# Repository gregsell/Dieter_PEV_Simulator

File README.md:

# dieter for EVerest PEV simulator
The EVerest PEV Simulator project documentation is split in two repositories:
1. the EVerest software running on linux, available at [gregsell/DieterEvDriver](https://github.com/gregsell/DieterEvDriver/)
2. this repo: electronics and firmware of the "Dieter" handling low level communication - *" Device Interface ElecTronic Especially not limited to Raspberry"*

demo: https://youtu.be/5YWvrdBq7K8?si=sz70jL9PTbtog_6K  
An essay covering the whole project is available under [gregsell/DieterEvDriver/docs/](https://github.com/gregsell/DieterEvDriver/) in english and german.  

## Hardware and Firmware for the Dieter PEV Simulator Board

This board is a physical interface between the [EVerest PEV Simulator](https://github.com/gregsell/DieterEvDriver/) software running on linux and a real CCS charging station. It generates and measures the IEC 61851 Control Pilot (CP) signal, drives the contactor and plug lock, and measures current and voltage on the HV lines.
The board is designed for DC charging test setups and capable of handling very high voltages.

The name and concept come from [uhi22/dieter](https://github.com/uhi22/dieter), a hardware design by Uwe Hennig. That project uses [pyPLC](https://github.com/uhi22/pyPLC) as simulation software. This repository adapts the hardware and uses an [EVerest](https://everest.github.io)-based software stack, which takes over the protocol logic from pyPLC.

## System Overview

## Hardware Components

The Arduino handles all low-level I/O relevant for CCS communication:

- **CP PWM measurement**: Fixed 5% duty cycle at 1 kHz (per IEC 61851-1) signals switch to high level communication by the EVSE
- **CP state control**: Sets CP voltage level to signal current state to EVSE during low-level communication
- **Contactor control**: Closes/opens the DC contactors on command from EVerest
- **Connector lock actuator**: Engages/releases the mechanical connector lock
- **Power meter**: Measures HV voltage and current

The Arduino communicates with the linux host over UART via USB using a simple text-based protocol, as implemented in the [`DieterEvDriver`](https://github.com/gregsell/DieterEvDriver/tree/main/modules/DieterEvDriver) EVerest module.
All the logic runs on the linux host. This board simply executes its commands and reads back measurements.

### HomePlug PLC Modem

In this project a patched TPlink TL-PA4010P v5.0 used (chipset: AR7420). (In the pyPLC project several modems were tested, see https://github.com/uhi22/pyPLC/blob/master/doc/hardware.md) The necessary modification steps are available there as well.   

The modem connects to the CP line and handles the high-level communication necessary for CCS. The Linux host runs `EvSlac` (EVerest module) for SLAC matching and PyEvJosev for the V2G ISO 15118-2 session over PLC.

## Arduino Serial Protocol
The Arduino exposes a simple newline-delimited text protocol over serial. The `DieterEvDriver` EVerest module running on the linux host speaks this protocol.
```
commands (host -> MCU)
  keys                   possible values            
  set_contactor             {0, 1}                            
  set_connector_lock        {0, 1}   
  set_state_c               {0, 1}

measurements (MCU -> host)
  u_inlet                   {0, 1, 2...}
  current                   {0.0, 1.0, 2.0,..}
  cp_duty_cycle             {0, 1, ..99, 100}
  connector_lock_confirmed  {0, 1}

each newline-terminated and separated by colon.

examples:
  "set_contactor:0\n"
  "u_inlet:800\n"
```
**Notes:**
- `current` is the only `float`, all the others are `integer`
- `set_state_c` might be misleading. In general there are more states, but this is the only one the EV can signal. (B <-> C)
- EVerest itself does not need current and voltage measurements

## Mounting
Mounting everything to a DIN rail (german "Hutschiene") makes it possible to use stock parts and be flexible with arrangement.

For the single PCBs adaptors were 3d printed to work with this design: https://www.printables.com/model/161740-din-rail-clip  
The source files are available under [/docs/mounting]().

Each clip can hold up to three M3 nuts spaced 9 mm apart and can be attached (and removed!) from the rail with a screwdriver. 

---

## Related Projects and useful links

- [uhi22/dieter](https://github.com/uhi22/dieter) — Original "Dieter" hardware firmware
- [uhi22/pyPLC](https://github.com/uhi22/pyPLC) — Python PLC/V2G stack, first open-source CCS implementation, also the hardware of the original "Dieter"
- [uhi22/foccci](https://github.com/uhi22/foccci) — open-source CCS controller, developed by openinverter community, runs a port of pyPLC
- [discussion on openinverter](https://openinverter.org/forum/viewtopic.php?p=37085) — homeplug investigations, beginnings of pyPLC
- [EVerest](https://github.com/EVerest/everest-core) — EV charging framework
- [charIn CCS design guide](https://www.charin.global/media/pages/technology/ccs-specification/c07034e41e-1626949173/design_guide_combined_charging_system_v7.pdf) — very useful. (Almost) everything you ever need to know about CCS
- [open-plc-utils](https://github.com/qca/open-plc-utils) — toolkit for patching PLC modem

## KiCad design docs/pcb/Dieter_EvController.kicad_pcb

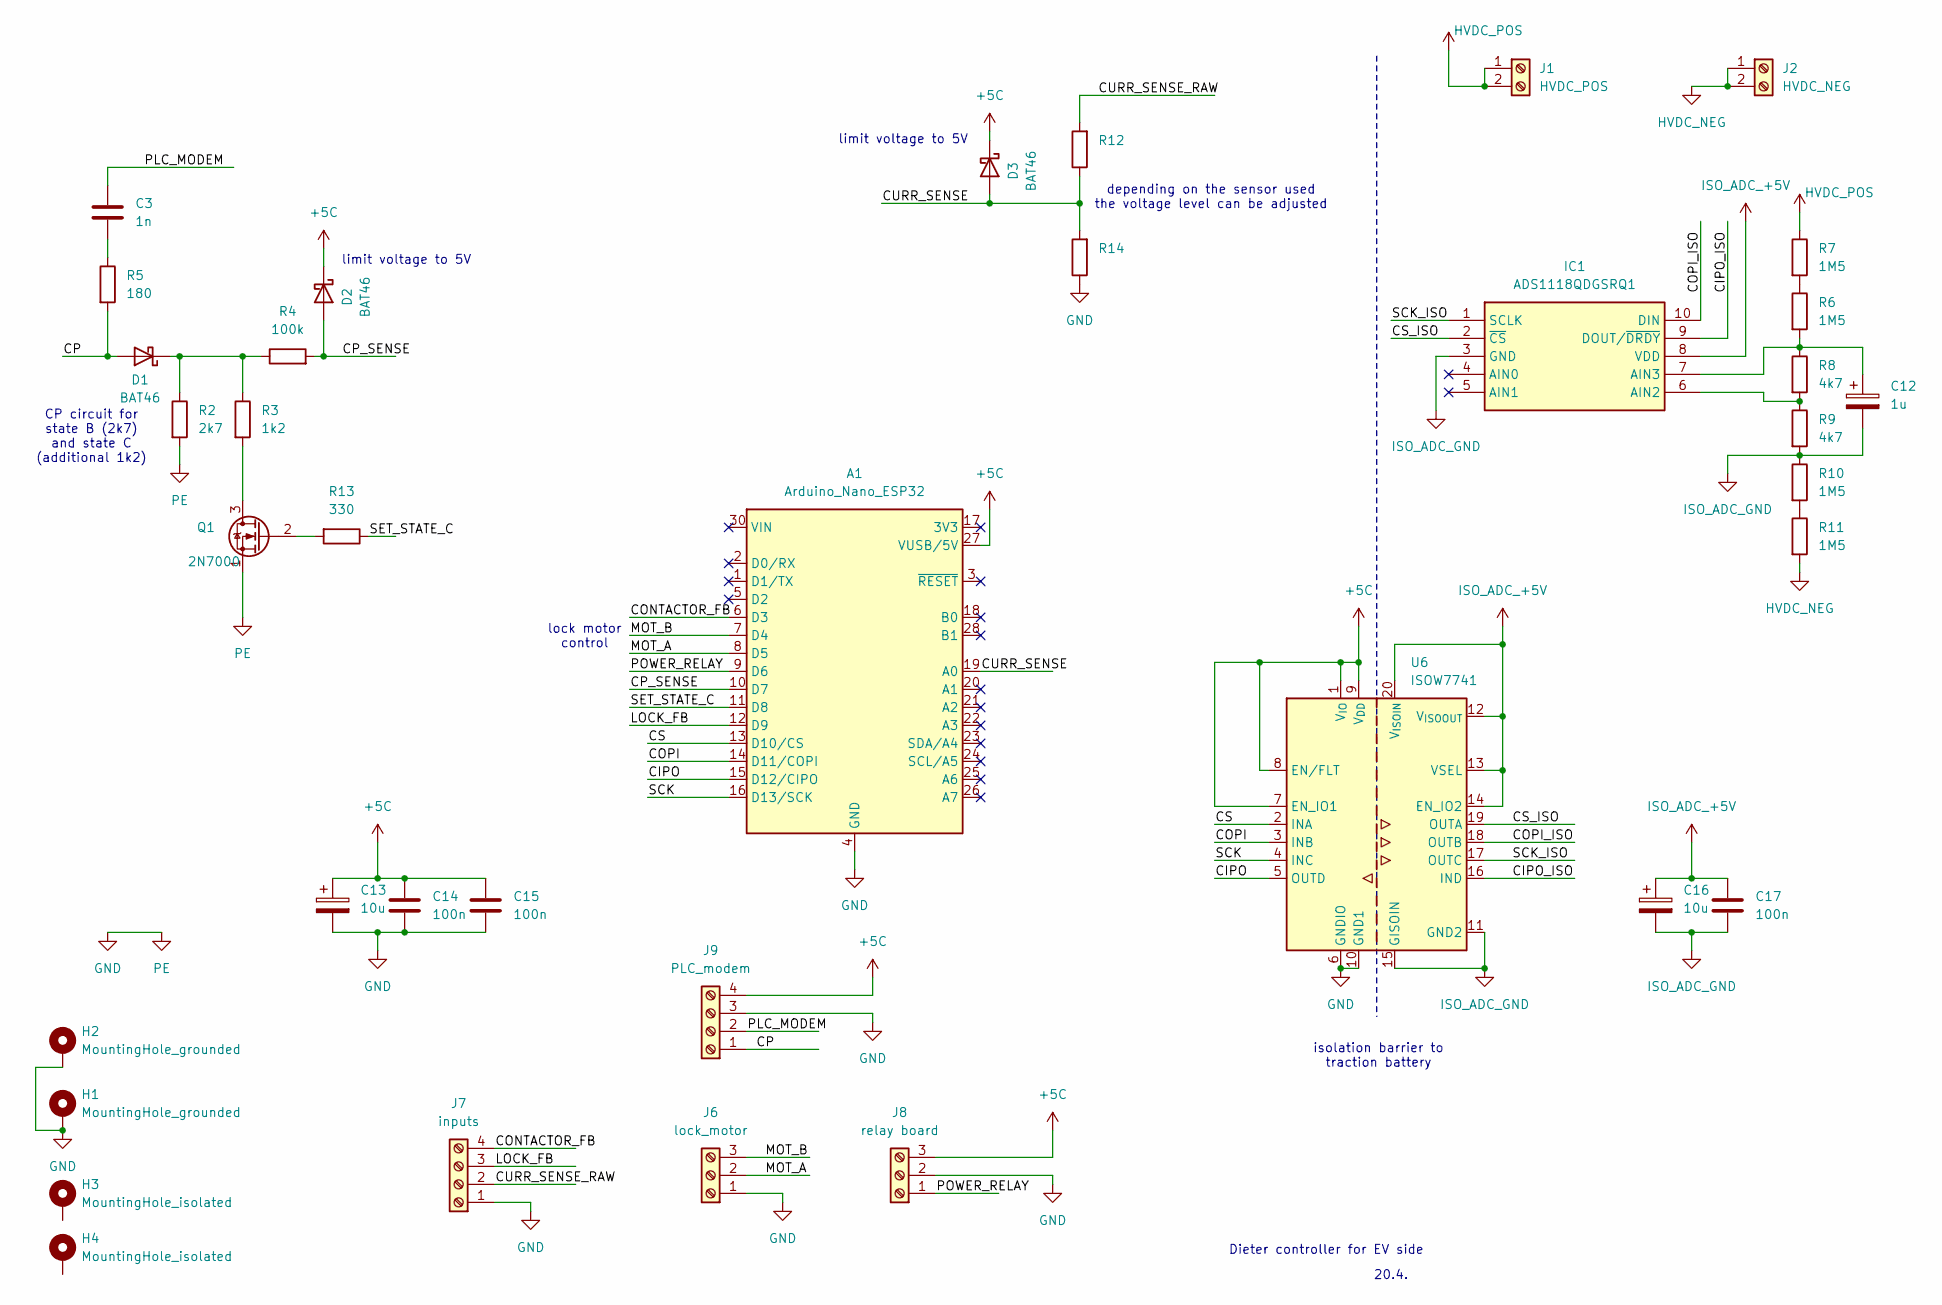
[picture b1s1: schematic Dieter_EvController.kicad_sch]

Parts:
A1: Arduino_Nano_ESP32; Arduino_Nano
C3: 1n; C_Disc_D5.0mm_W2.5mm_P5.00mm
C12: 1u; CP_Radial_D5.0mm_P2.00mm
C13, C16: 10u; CP_Radial_D5.0mm_P2.00mm
C14, C15, C17: 100n; C_Disc_D5.0mm_W2.5mm_P5.00mm
D1, D2, D3: BAT46; D_DO-35_SOD27_P7.62mm_Horizontal
H1, H2: MountingHole_grounded; MountingHole_3.2mm_M3_Pad_TopBottom
H3, H4: MountingHole_isolated
IC1: ADS1118QDGSRQ1; SOP50P490X110-10N; Mouser Part Number 595-ADS1118QDGSRQ1
J1: HVDC_POS; TerminalBlock_MaiXu_MX126-5.0-02P_1x02_P5.00mm
J2: HVDC_NEG; TerminalBlock_MaiXu_MX126-5.0-02P_1x02_P5.00mm
J6: lock_motor; TerminalBlock_MaiXu_MX126-5.0-03P_1x03_P5.00mm
J7: inputs; TerminalBlock_MaiXu_MX126-5.0-04P_1x04_P5.00mm
J8: relay board; TerminalBlock_MaiXu_MX126-5.0-03P_1x03_P5.00mm
J9: PLC_modem; TerminalBlock_MaiXu_MX126-5.0-04P_1x04_P5.00mm
Q1: 2N7000; TO-92_Inline
R2: 2k7; R_Axial_DIN0204_L3.6mm_D1.6mm_P7.62mm_Horizontal
R3: 1k2; R_Axial_DIN0204_L3.6mm_D1.6mm_P7.62mm_Horizontal
R4, R12, R14: 100k; R_Axial_DIN0204_L3.6mm_D1.6mm_P7.62mm_Horizontal
R5: 180; R_Axial_DIN0204_L3.6mm_D1.6mm_P7.62mm_Horizontal
R6, R7, R10, R11: 1M5; R_Axial_DIN0204_L3.6mm_D1.6mm_P7.62mm_Horizontal
R8, R9: 4k7; R_Axial_DIN0204_L3.6mm_D1.6mm_P7.62mm_Horizontal
R13: 330; R_Axial_DIN0204_L3.6mm_D1.6mm_P7.62mm_Horizontal
U6: ISOW7741; SOIC-20W_7.5x12.8mm_P1.27mm

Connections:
+5C: A1.27 (VUSB/5V), C13.1, C14.1, C15.1, D2.1 (K), D3.1 (K), J8.3, J9.4, U6.1 (V_{IO}), U6.7 (EN_IO1), U6.8 (EN/FLT), U6.9 (V_{DD})
/CIPO: A1.15 (D12/CIPO), U6.5 (OUTD)
/CIPO_ISO: IC1.9 (DOUT/~DRDY), U6.16 (IND)
/CONTACTOR_FB: A1.6 (D3), J7.4
/COPI: A1.14 (D11/COPI), U6.3 (INB)
/COPI_ISO: IC1.10 (DIN), U6.18 (OUTB)
/CP: D1.2 (A), J9.1, R5.2
/CP_SENSE: A1.10 (D7), D2.2 (A), R4.2
/CS: A1.13 (D10/CS), U6.2 (INA)
/CS_ISO: IC1.2 (~CS), U6.19 (OUTA)
/CURR_SENSE: A1.19 (A0), D3.2 (A), R12.1, R14.2
/CURR_SENSE_RAW: J7.2, R12.2
/LOCK_FB: A1.12 (D9), J7.3
/MOT_A: A1.8 (D5), J6.2
/MOT_B: A1.7 (D4), J6.3
/PLC_MODEM: C3.1, J9.2
/POWER_RELAY: A1.9 (D6), J8.1
/SCK: A1.16 (D13/SCK), U6.4 (INC)
/SCK_ISO: IC1.1 (SCLK), U6.17 (OUTC)
/SET_STATE_C: A1.11 (D8), R13.1
GND: A1.4 (GND), A1.29 (GND), C13.2, C14.2, C15.2, H1.1 (1_1), H2.1 (1_1), J6.1, J7.1, J8.2, J9.3, Q1.1 (S), R2.2, R14.1, U6.6 (GNDIO), U6.10 (GND1)
HVDC_NEG: J2.1, J2.2, R11.2
HVDC_POS: J1.1, J1.2, R7.1
ISO_ADC_+5V: C16.1, C17.1, IC1.8 (VDD), U6.12 (V_{ISOOUT}), U6.13 (VSEL), U6.14 (EN_IO2), U6.20 (V_{ISOIN})
ISO_ADC_GND: C12.2, C16.2, C17.2, IC1.3 (GND), R9.2, R10.1, U6.11 (GND2), U6.15 (GISOIN)
unnamed: C3.2, R5.1
unnamed: D1.1 (K), R2.1, R3.1, R4.1
unnamed: IC1.6 (AIN2), R8.2, R9.1
unnamed: C12.1, IC1.7 (AIN3), R6.2, R8.1
unnamed: Q1.3 (D), R3.2
unnamed: Q1.2 (G), R13.2
unnamed: R6.1, R7.2
unnamed: R10.2, R11.1

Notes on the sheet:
CP circuit for state B (2k7) and state C (additional 1k2)
20.4.
depending on the sensor used the voltage level can be adjusted
limit voltage to 5V
lock motor control
Dieter controller for EV side
isolation barrier to traction battery

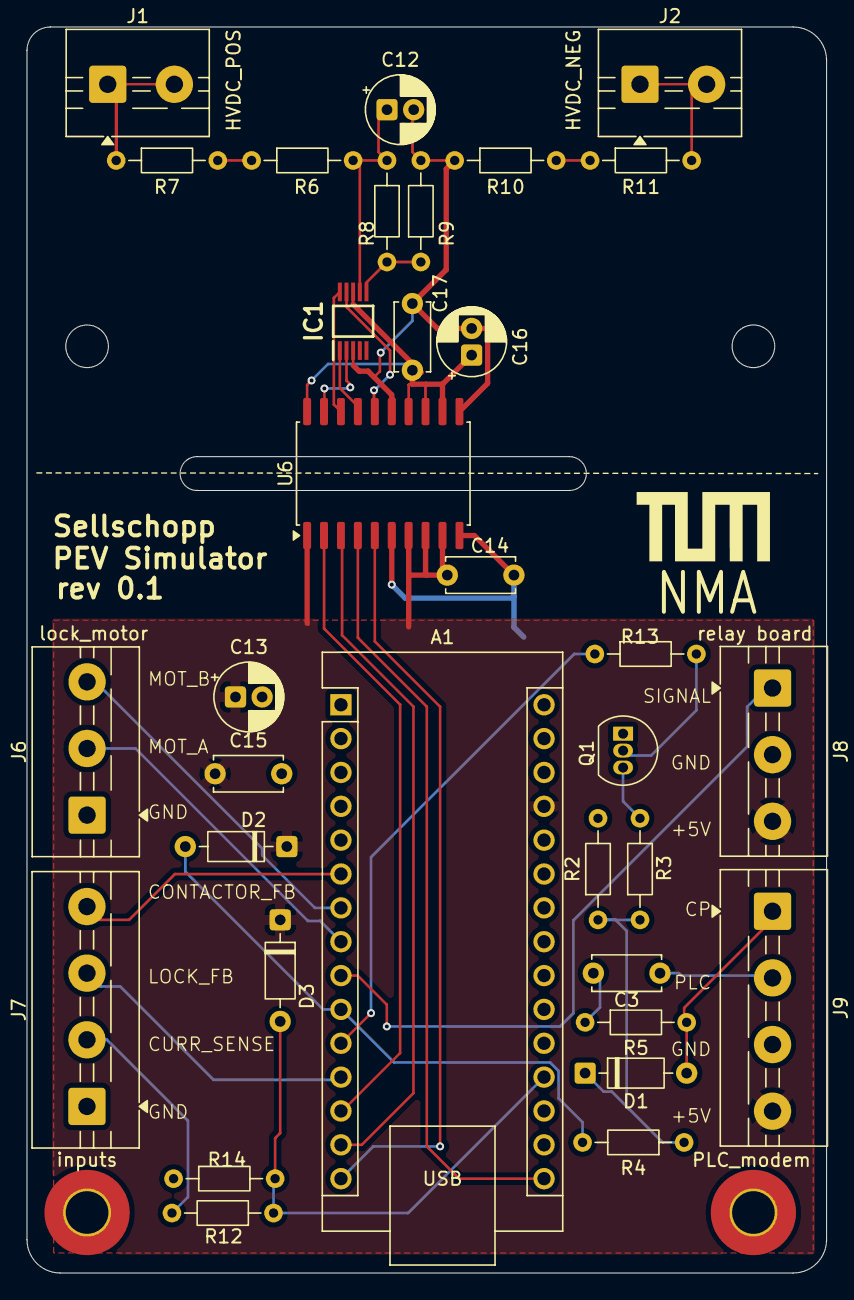
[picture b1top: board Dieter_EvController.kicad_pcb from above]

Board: 2 copper layers, 60.0 x 93.5 mm, 35 parts (0 on the bottom side), 33 nets.

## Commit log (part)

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2026-04-11 chore: init
2026-04-11 chore: update .gitignore
2026-04-11 parse measurements: high voltage (not complete yet) Cp pin duty cycle feedback from CCS connector lock
    handles the following commands
    set Cp state
    set connector lock state (not complete yet)
    set contactor state
    add documentation to protocol
2026-04-12 fix: drop transmit of cp state, control by bool set_state_c now
2026-04-14 chore: change to uno, try out serial monitor flags
2026-04-14 chore: add dummy values, add comments
2026-04-14 fix: cmd string to int conversion
2026-05-05 refractor: change name to connector_lock_confirmed
2026-05-05 feat: lock motor control
2026-05-05 chore: delete set_contactor
2026-05-10 chore: update PINs according to schematic
2026-05-22 add external ADC + current readout
2026-05-22 refractor: details + method comments
2026-05-22 chore: add electronics docs
2026-05-22 chore: remove compile_commands from gitignore, delete empty folders documentation: fancy README, pcb + mounting source files
2026-06-02 feat: connector lock works
2026-06-02 documentation: readme overview paragraph + license
2026-06-02 documentation: add mounting + corrected pcb source files; BOM
